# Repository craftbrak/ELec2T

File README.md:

# ELec2T

lien du raport intermediaire : https://docs.google.com/document/d/1l9kerCUgm6wP6RkYXObC0R5gBAUdyCEyKLtMM8cPomE/edit?usp=sharing

lien du cahier des charges : /

lien du Trello: https://trello.com/b/0pvsDK53/main

lien du rapport final https://docs.google.com/document/d/1BPvHGJe16M144FmVLOqQ-wgt9hW2KqvDGt-wu0VLWqM/edit#

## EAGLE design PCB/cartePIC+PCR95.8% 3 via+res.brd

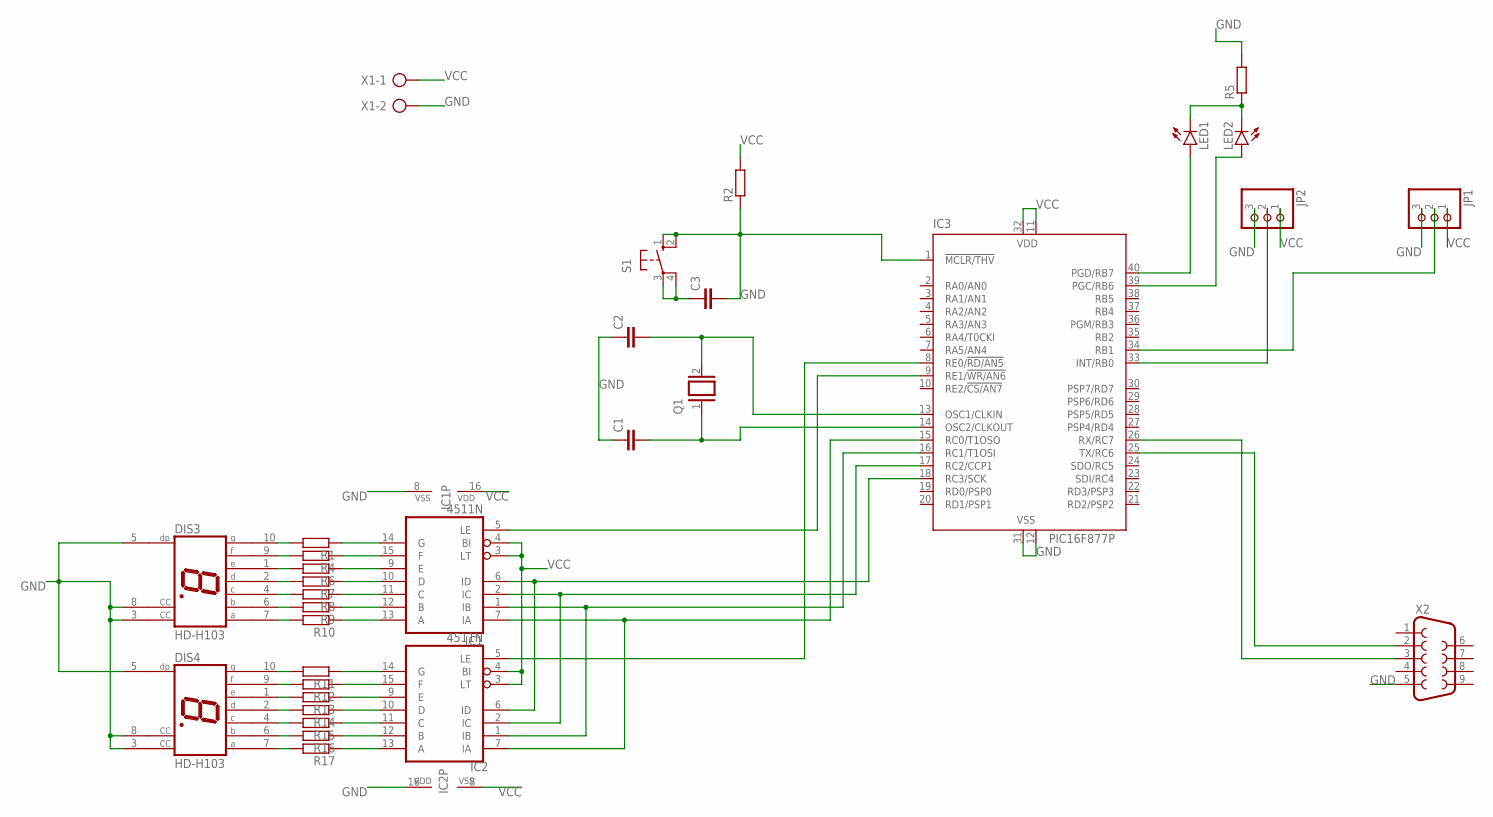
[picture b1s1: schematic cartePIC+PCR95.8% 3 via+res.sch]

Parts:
C1, C2, C3: C-EU025-025X050; C025-025X050
DIS3, DIS4: HD-H103; HDSP-M
IC1, IC2: 4511N; DIL16
IC3: PIC16F877P; DIL40
JP1, JP2: PINHD-1X3; 1X03
LED1, LED2: LED5MM
Q1: XTAL/S; QS
R1, R2, R4, R5, R6, R7, R8, R9, R10, R11, R12, R13, R14, R15, R16, R17: R-EU_0207/10; 0207/10
S1: 10-XX; B3F-10XX
X1: AK300/2
X2: F09H

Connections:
GND: C1.1, C2.1, C3.2, DIS3.3 (CC), DIS3.5 (DP), DIS3.8 (CC), DIS4.3 (CC), DIS4.5 (DP), DIS4.8 (CC), IC1.8 (VSS), IC2.16 (VDD), IC3.1 (!MCLR/THV), IC3.12 (VSS), IC3.31 (VSS), JP1.3, JP2.3, R2.1, R5.2, S1.1 (S), S1.2 (S1), X1.2, X2.5
unnamed: IC1.5 (LE), IC3.9 (RE1/!WR/AN6)
unnamed: IC2.5 (LE), IC3.8 (RE0/!RD/AN5)
unnamed: IC1.6 (ID), IC2.6 (ID), IC3.18 (RC3/SCK)
unnamed: IC1.2 (IC), IC2.2 (IC), IC3.17 (RC2/CCP1)
unnamed: IC1.1 (IB), IC2.1 (IB), IC3.16 (RC1/T1OSI)
unnamed: IC1.7 (IA), IC2.7 (IA), IC3.15 (RC0/T1OSO)
unnamed: C2.2, IC3.13 (OSC1/CLKIN), Q1.2
unnamed: C1.2, IC3.14 (OSC2/CLKOUT), Q1.1
unnamed: IC1.14 (G), R1.1
unnamed: IC1.15 (F), R4.1
unnamed: IC1.9 (E), R6.1
unnamed: IC1.10 (D), R7.1
unnamed: IC1.11 (C), R8.1
unnamed: IC1.12 (B), R9.1
unnamed: IC1.13 (A), R10.1
unnamed: IC2.14 (G), R11.1
unnamed: IC2.15 (F), R12.1
unnamed: IC2.9 (E), R13.1
unnamed: IC2.10 (D), R14.1
unnamed: IC2.11 (C), R15.1
unnamed: IC2.12 (B), R16.1
unnamed: IC2.13 (A), R17.1
unnamed: IC3.33 (INT/RB0), JP2.2
unnamed: C3.1, S1.3, S1.4 (P1)
unnamed: IC3.34 (RB1), JP1.2
unnamed: IC3.40 (PGD/RB7), LED1.A
unnamed: IC3.25 (TX/RC6), X2.2
unnamed: IC3.26 (RX/RC7), X2.3
unnamed: IC3.39 (PGC/RB6), LED2.A
unnamed: LED1.K (C), LED2.K (C), R5.1
unnamed: DIS3.10 (G), R1.2
unnamed: DIS3.9 (F), R4.2
unnamed: DIS3.1 (E), R6.2
unnamed: DIS3.2 (D), R7.2
unnamed: DIS3.4 (C), R8.2
unnamed: DIS3.6 (B), R9.2
unnamed: DIS3.7 (A), R10.2
unnamed: DIS4.10 (G), R11.2
unnamed: DIS4.9 (F), R12.2
unnamed: DIS4.1 (E), R13.2
unnamed: DIS4.2 (D), R14.2
unnamed: DIS4.4 (C), R15.2
unnamed: DIS4.6 (B), R16.2
unnamed: DIS4.7 (A), R17.2
VCC: IC1.3 (LT), IC1.4 (BI), IC1.16 (VDD), IC2.3 (LT), IC2.4 (BI), IC2.8 (VSS), IC3.11 (VDD), IC3.32 (VDD), JP1.1, JP2.1, R2.2, X1.1

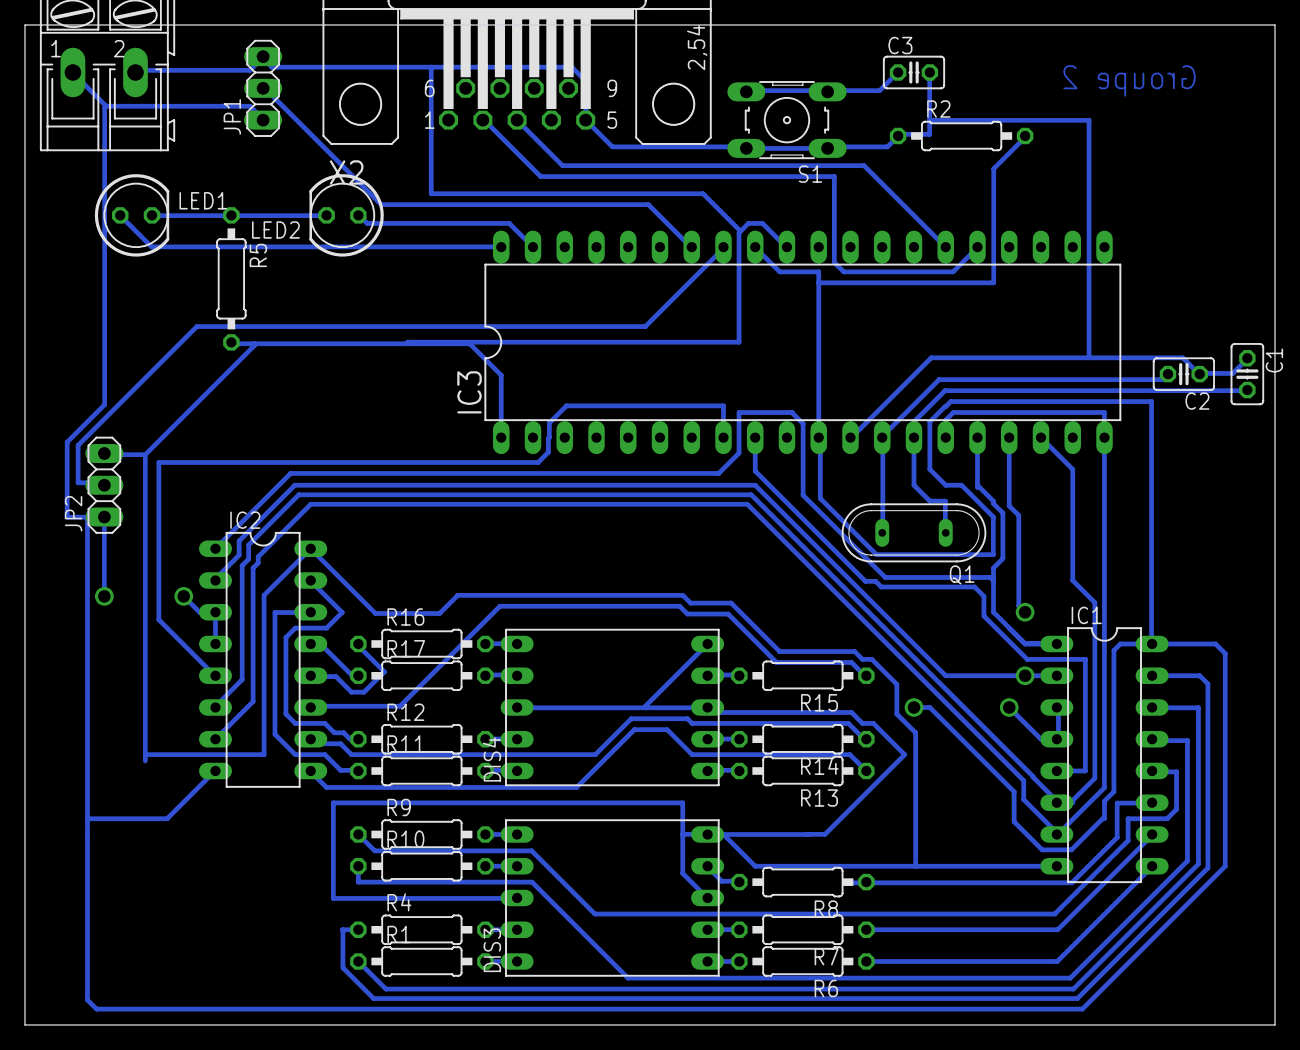
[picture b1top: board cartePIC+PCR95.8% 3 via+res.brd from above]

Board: 2 copper layers, 100.0 x 80.0 mm, 32 parts (0 on the bottom side), 46 nets.

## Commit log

2021-02-15 first push Proteus
2021-02-17 ajout des composant
2021-02-17 test c + circuit
2021-02-18 update simulation
2021-02-18 7segment decodeur +code
2021-02-19 aded PIR test
2021-02-19 test COMPIM send
2021-02-19 config COMPIN simu
2021-02-22 start eagle
2021-02-22 test C
2021-02-24 update c code
2021-02-24 Revert "update c code"
    This reverts commit 3213a62ca6c0ad99c1b1cb5e572727f73b6a3c1a.
2021-02-27 update sim +PCB
2021-02-27 final PCB
2021-02-27 correction erreur nom groupe + vertion avec resistance
2021-02-28 Final Board
2021-03-03 up python
2021-03-03 remove test project
2021-03-03 Ignore weird CCS files
2021-03-03 Create C project
2021-03-03 Move display to its own unit
2021-03-03 Fix master reset
2021-03-03 Fix underflow :neutral_face:
2021-03-04 compile project
2021-03-09 up python kivy
2021-03-12 added connector for alarm on the board
2021-05-02 python threading not finished
2021-05-03 Fix RDA conflict with display
2021-05-10 Maj python fonctionnel et fini
2021-05-10 ajout image pour python
